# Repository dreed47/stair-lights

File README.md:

# Smart Staircase Lighting

DIY staircase lighting with capacitive touch detection and Home Assistant integration. Touch the handrail → lights fade in. Walk away → lights fade out. All settings tunable live via HA sliders.

---

## How It Works

1. Copper tape runs along the underside of the handrail, wired to **GPIO1** on the ESP32-S2 Mini as a capacitive touch sensor.
2. Touch triggers `handle_stair_timer` — a configurable filter-on delay confirms it's a real touch (not noise).
3. **GPIO18** drives an **IRLZ44N MOSFET** via PWM, which powers a **COB LED strip** with a smooth 1-second fade-in.
4. After the configured duration, lights fade out over 4 seconds.
5. Touching again during the timer restarts it (script `mode: restart`).

The COB strip gives a seamless "dot-less" glow. All wiring is routed internally through the wall with low-profile silicone grommets — hardware stays invisible.

---

## Hardware

| Component | Details |
| --- | --- |
| MCU | Wemos S2 Mini (ESP32-S2) |
| MOSFET | IRLZ44N (logic-level, TO-220) |
| LED Strip | COB (chip-on-board), single color |
| Touch Sensor | Copper tape on handrail → GPIO1 |
| PWM Output | GPIO18 → MOSFET gate |
| PCB | Custom KiCad design (see `hardware/kicad/`) |

---

## Firmware

Built with [ESPHome](https://esphome.io). No custom C++ — pure YAML.

### Flash

```bash
# Install ESPHome if needed
pip install esphome

# Add WiFi credentials
cp firmware/secrets.yaml.example firmware/secrets.yaml
# edit firmware/secrets.yaml with your SSID and password

# Flash
esphome run firmware/stairlights.yaml
```

`secrets.yaml` format:

```yaml
wifi_ssid: "YourNetwork"
wifi_password: "YourPassword"
```

After first flash, OTA updates work over WiFi — no USB needed.

---

## Home Assistant Controls

Once the ESPHome integration is added in HA, five sliders appear:

| Slider | Range | Default | Purpose |
| --- | --- | --- | --- |
| **Light Duration** | 5–120 s | 30 s | How long lights stay on after touch |
| **LED Brightness** | 10–100 % | 100 % | Peak brightness at fade-in |
| **Touch Threshold** | 1,000–300,000 | 50,000 | Capacitive trigger level — tune for your handrail |
| **Touch Filter On** | 0–100 ms | 8 ms | Debounce delay before turning on (rejects noise) |
| **Touch Filter Off** | 0–100 ms | 50 ms | Extra hang time before starting fade-out |

**Calibrating touch sensitivity:** Start with Touch Threshold at 50,000. Watch the `Staircase Touch Pad` binary sensor in HA. Raise the threshold if lights trigger from ambient noise/humidity; lower it if touches aren't registering.

---

## Wiring

See `docs/schematic.png` for the full Cirkit Designer diagram. Key connections:

```text
ESP32-S2 GPIO18  →  IRLZ44N Gate (via 10Ω resistor)
IRLZ44N Drain   →  LED Strip negative
LED Strip +     →  12V supply
IRLZ44N Source  →  GND
ESP32-S2 GPIO1  →  Copper tape (touch sensor)
ESP32-S2 GND   →  GND
ESP32-S2 3.3V  →  (internal, no external connection needed)
```

---

## File Structure

```text
stair-lights/
├── firmware/
│   └── stairlights.yaml        # ESPHome configuration
├── hardware/
│   ├── kicad/                  # KiCad schematic and PCB layout
│   │   ├── StairLights.kicad_pcb
│   │   ├── StairLights.kicad_pro
│   │   ├── StairLights.kicad_prl
│   │   └── StairLights.kicad_sch
│   ├── gerbers/
│   │   └── StairLights.kicad_pcb.zip   # Fabrication-ready Gerbers
│   └── stairs-pcb.step         # 3D model
└── docs/
    ├── schematic.png            # Wiring diagram
    ├── esp32-s2-mini-front.png  # MCU reference photo
    └── esp32-s2-mini-back.png   # MCU pinout
```

---

## Troubleshooting

**Lights trigger randomly** — Capacitive drift from humidity or power fluctuations. Raise Touch Threshold or increase Touch Filter On delay.

**Touch not registering** — Lower Touch Threshold. Ensure copper tape has good contact with the GPIO1 wire.

**Fallback AP** — If WiFi is unreachable, the ESP32 broadcasts `Stairlights Fallback Hotspot`. Connect to it and navigate to `192.168.4.1` to reconfigure.

**OTA fails** — Make sure `secrets.yaml` OTA password matches what was flashed. Default is in the YAML.

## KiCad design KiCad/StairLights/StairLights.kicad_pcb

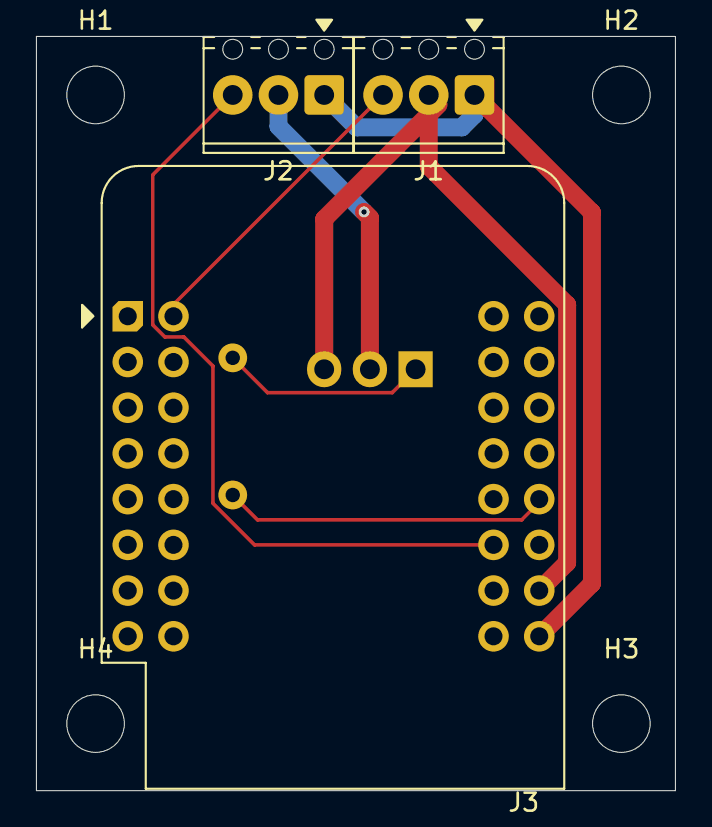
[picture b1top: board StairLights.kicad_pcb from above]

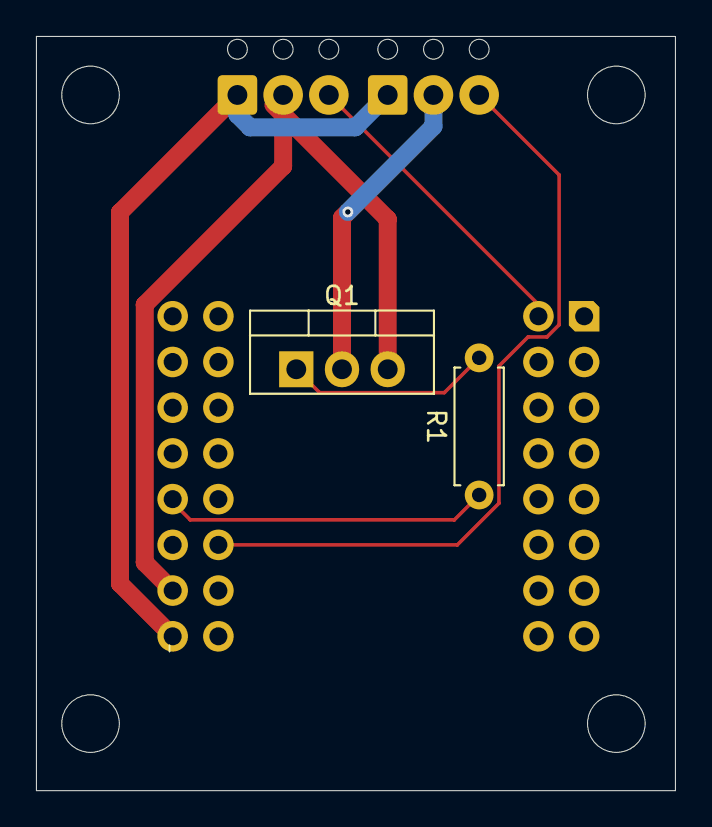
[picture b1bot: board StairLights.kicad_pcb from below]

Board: 2 copper layers, 35.5 x 41.9 mm, 9 parts (2 on the bottom side), 7 nets.

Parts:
H1, H2, H3, H4: MountingHole; MountingHole_3.2mm_M3
J1, J2: Screw_Terminal_01x03; TerminalBlock_Phoenix_MPT-0,5-3-2.54_1x03_P2.54mm_Horizontal
J3: Conn_01x05; wemoss2
Q1: IRLZ44N; TO-220-3_Vertical
R1: 10K; R_Axial_DIN0207_L6.3mm_D2.5mm_P7.62mm_Horizontal

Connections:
/GATE_IN: Q1.1 (G), R1.2
/GATE_OUT: J3.12, R1.1
/GND: J1.2, J3.10, Q1.3 (S)
/LED_NEG: J2.2, Q1.2 (D)
/PWR_5V: J1.1, J2.1, J3.9
unnamed: J1.3, J3.17
unnamed: J2.3, J3.27

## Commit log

2026-05-10 inital working
2026-05-10 better touch trigger time
2026-05-11 first test on handrail - working
2026-05-11 added more HA config fields
2026-05-11 Update .gitignore to ignore .hosrty folder and KiCad backups
2026-05-11 Fix .gitignore to properly ignore .history folder
2026-05-11 fixes
2026-05-11 added docs
2026-05-15 updetes
